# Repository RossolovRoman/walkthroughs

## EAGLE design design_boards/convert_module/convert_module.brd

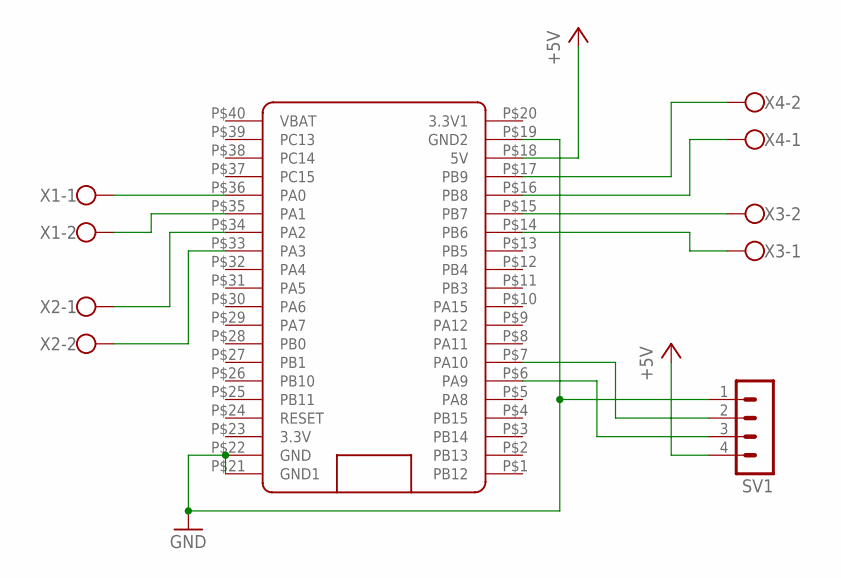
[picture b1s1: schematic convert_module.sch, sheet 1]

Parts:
SV1: MA04-1
U$1: BLUE_PILL
X1, X2, X3, X4: W237-102

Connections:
+5V: SV1.4, U$1.P$18 (5V); also elsewhere on the board
GND: SV1.1, U$1.P$19 (GND2), U$1.P$21 (GND1), U$1.P$22 (GND); also elsewhere on the board
unnamed: U$1.P$17 (PB9), X4.2
unnamed: U$1.P$16 (PB8), X4.1
unnamed: U$1.P$15 (PB7), X3.2
unnamed: U$1.P$14 (PB6), X3.1
unnamed: SV1.2, U$1.P$7 (PA10)
unnamed: U$1.P$36 (PA0), X1.1
unnamed: U$1.P$35 (PA1), X1.2
unnamed: U$1.P$34 (PA2), X2.1
unnamed: U$1.P$33 (PA3), X2.2
unnamed: SV1.3, U$1.P$6 (PA9)

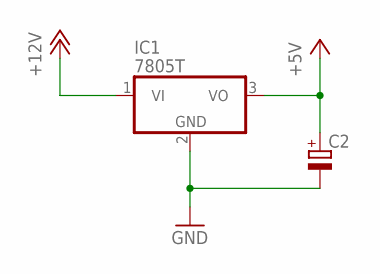
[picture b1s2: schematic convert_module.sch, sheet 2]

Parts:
C2: CPOL-EUE2.5-5; E2,5-5
IC1: 7805T; TO220H

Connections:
+5V: C2.+, IC1.3 (VO); also elsewhere on the board
+12V: IC1.1 (VI); also elsewhere on the board
GND: C2.-, IC1.2 (GND); also elsewhere on the board

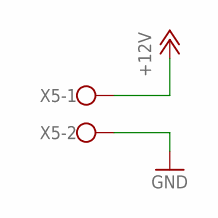
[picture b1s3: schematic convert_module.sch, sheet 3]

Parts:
X5: W237-102

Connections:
+12V: X5.1; also elsewhere on the board
GND: X5.2; also elsewhere on the board

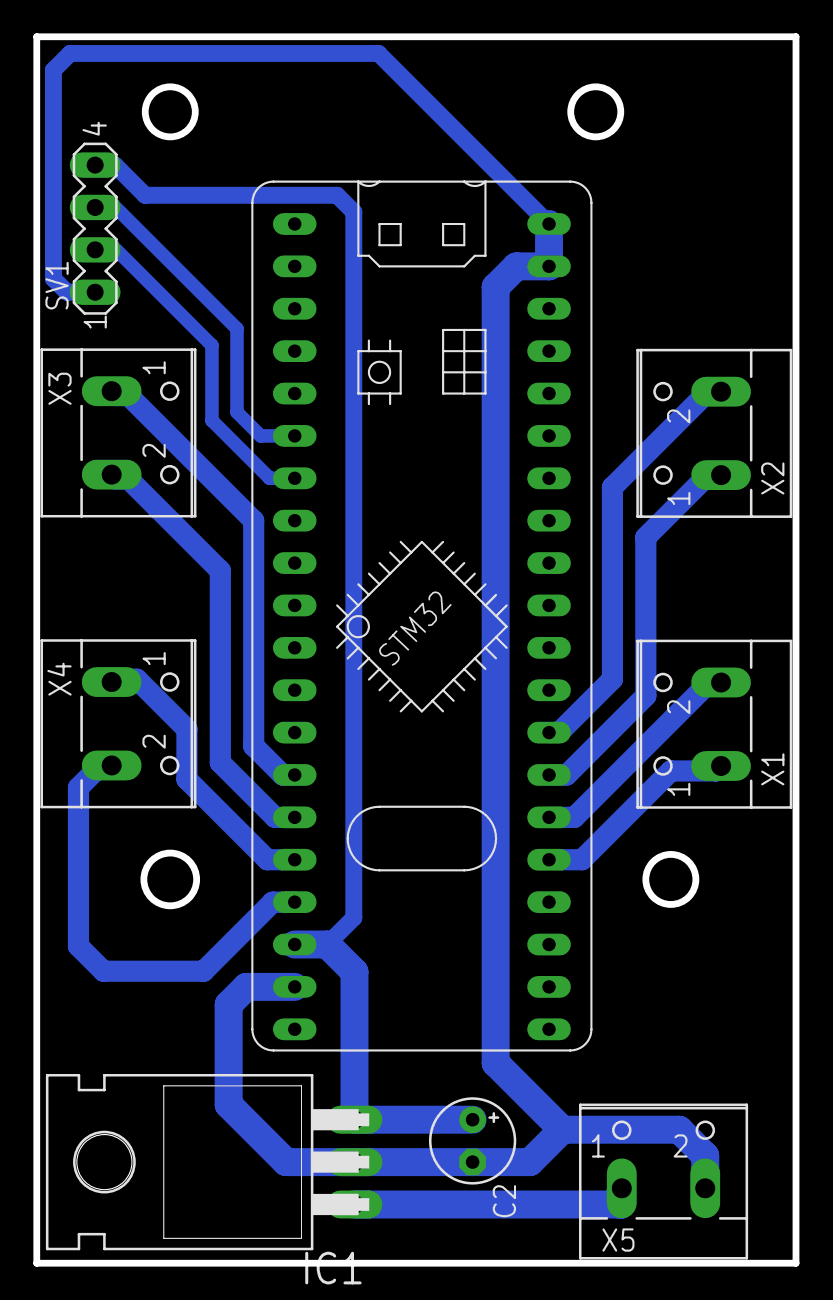
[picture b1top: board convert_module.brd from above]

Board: 2 copper layers, 45.5 x 73.5 mm, 9 parts (0 on the bottom side), 13 nets.

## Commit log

2019-07-20 Добавлена библиотека преобразования Wiegand37 > Wiegand34. Добавлены инструкции по прошивке STM32. Добавлены эл. схема и плата устройства.
